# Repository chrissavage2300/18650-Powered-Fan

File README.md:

# 18650-Powered-Fan

This project was created for the sole purpose of cooling down oatmeal or other things.

Features a charging IC and boost converter. Four LEDs show either power,charging,done or low battery. Has a PTC fuse to protect
the battery from overcharging. 

Run time (2000mAh Battery):20 Hours

BOM link: http://www.digikey.com/short/jm2fbp

5/19/2018

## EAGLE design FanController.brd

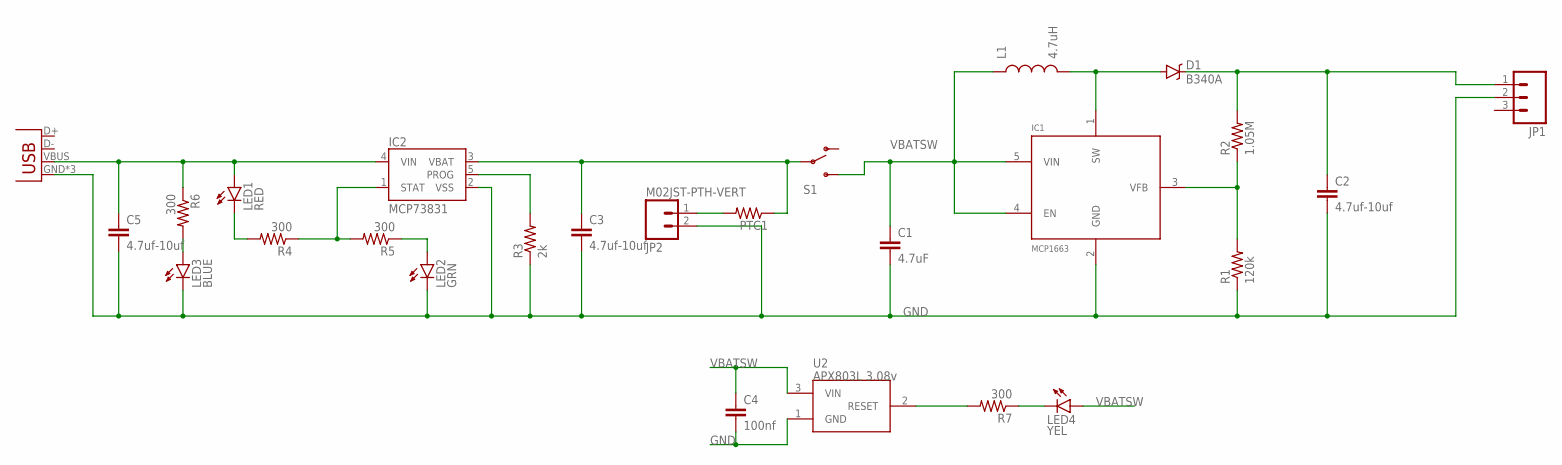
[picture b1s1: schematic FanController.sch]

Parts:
C1: 4.7uF; 1206
C2, C3, C5: 4.7uf-10uf; 1206
C4: 100nf; 1206
D1: B340A; SMA-DIODE
IC1: MCP1663; SOT23-5
IC2: MCP73831; SOT23-5
JP1: M03POLAR_LOCK; MOLEX-1X3_LOCK
JP2: M02JST-PTH-VERT; JST-2-PTH-VERT
JP3: USB-MICROB
L1: 4.7uH; 1210
LED1: RED; LED-1206
LED2: GRN; LED-1206
LED3: BLUE; LED-1206
LED4: YEL; LED-1206
PTC1: RESISTOR1206; 1206
R1: 120k; 1206
R2: 1.05M; 1206
R3: 2k; 1206
R4, R5, R6, R7: 300; 1206
S1: SWITCH-SPDTKIT; SWITCH-SPDT_KIT
U2: APX803L 3.08v; SOT23

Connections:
GND: C1.2, C2.2, C3.2, C4.2, C5.2, IC1.2 (GND), IC2.2 (VSS), JP1.2, JP2.2, JP3.GND, JP3.MT1 (GND), JP3.MT2 (GND), LED2.C, LED3.C, R1.1, R3.1, U2.1 (GND)
unnamed: D1.A, IC1.1 (SW), L1.2
unnamed: JP2.1, PTC1.2
unnamed: LED1.C, R4.2
unnamed: C2.1, D1.C, JP1.1, R2.2
unnamed: IC1.3 (VFB), R1.2, R2.1
unnamed: IC2.1 (STAT), R4.1, R5.2
unnamed: IC2.5 (PROG), R3.2
unnamed: C5.1, IC2.4 (VIN), JP3.VBUS, LED1.A, R6.1
unnamed: LED2.A, R5.1
unnamed: R7.2, U2.2 (RESET)
unnamed: LED3.A, R6.2
unnamed: LED4.C, R7.1
VBATSW: C1.1, C4.1, IC1.4 (EN), IC1.5 (VIN), L1.1, LED4.A, S1.3 (S), U2.3 (VIN)
VCHARGE: C3.1, IC2.3 (VBAT), PTC1.1, S1.2

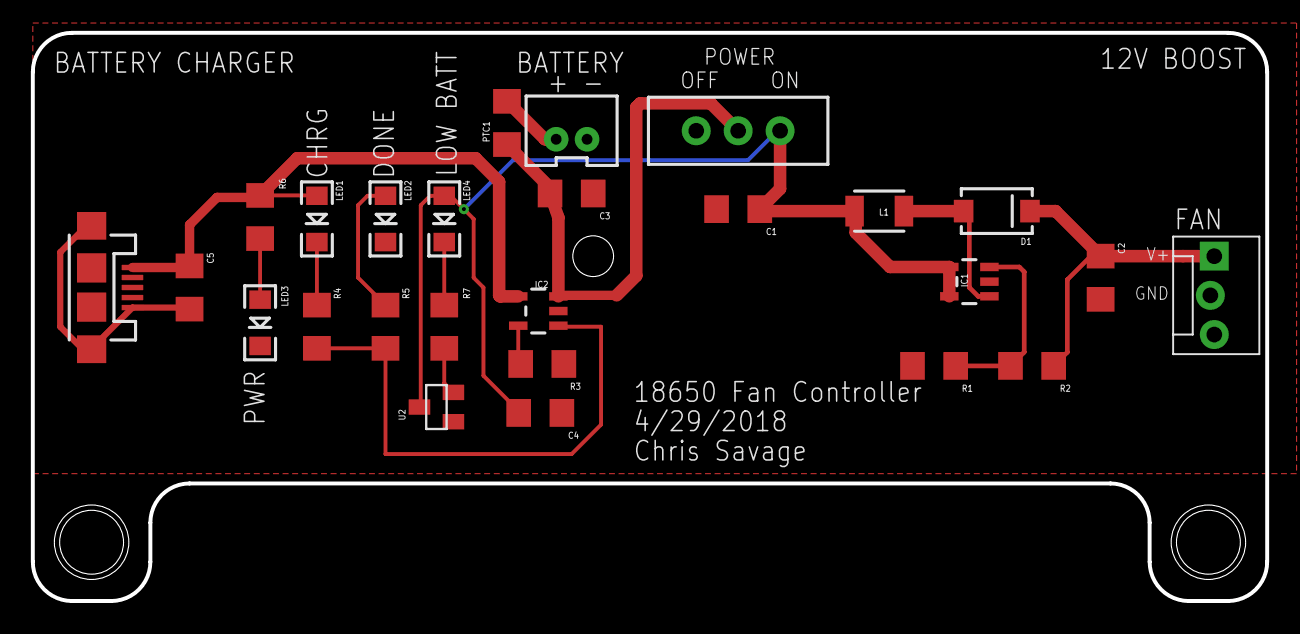
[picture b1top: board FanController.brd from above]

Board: 2 copper layers, 80.0 x 36.8 mm, 26 parts (0 on the bottom side), 15 nets.

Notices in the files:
parts and their libraries:
SparkFun-Capacitors: Licensing: Creative Commons ShareAlike 4.0 International - https://creativecommons.org/licenses/by-sa/4.0
